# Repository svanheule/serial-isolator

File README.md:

# Dual serial isolator

Small board design for a single MAX12930/MAX12931 isolator chip.

Since the MAX12930 and MAX12931 have a similar pin-out, a single board can be
used to expose their input and output pins. The spacing of the board's pin rows
is chosen such that the board can easily be mounted on a breadboard.

The back side of the board has two areas you can use to indicate in which
direction the signals can go, depending on which chip you used to populate the
board with.

Note that there is no reverse voltage protection included, so always pay
attention when hooking up VCC/GND.

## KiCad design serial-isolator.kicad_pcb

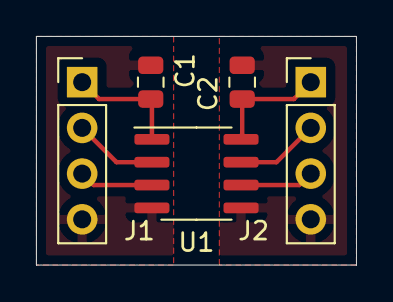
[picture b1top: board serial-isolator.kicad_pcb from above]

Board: 2 copper layers, 17.8 x 12.7 mm, 5 parts (0 on the bottom side), 8 nets.

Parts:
C1, C2: 1u; C_0805_2012Metric
J1, J2: Conn_01x04_Male; PinHeader_1x04_P2.54mm_Vertical
U1: MAX12930; SOIC-8_3.9x4.9mm_P1.27mm

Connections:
GND1: C1.1, J1.4, U1.4
GND2: C2.1, J2.4, U1.5
unnamed: J1.2, U1.2
unnamed: J1.3, U1.3
unnamed: J2.2, U1.7
unnamed: J2.3, U1.6
VCC: C1.2, J1.1, U1.1
VSS: C2.2, J2.1, U1.8

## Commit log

2021-04-04 Add design files and README
2021-04-05 Improve documentation
